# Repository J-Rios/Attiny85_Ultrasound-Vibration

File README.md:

# Attiny85_Ultrasound-Vibration
Attiny85 based system that read an ultrasound sensor and determines the distance by turning on a mini dc motor vibrator.
[See image.](Image.png)

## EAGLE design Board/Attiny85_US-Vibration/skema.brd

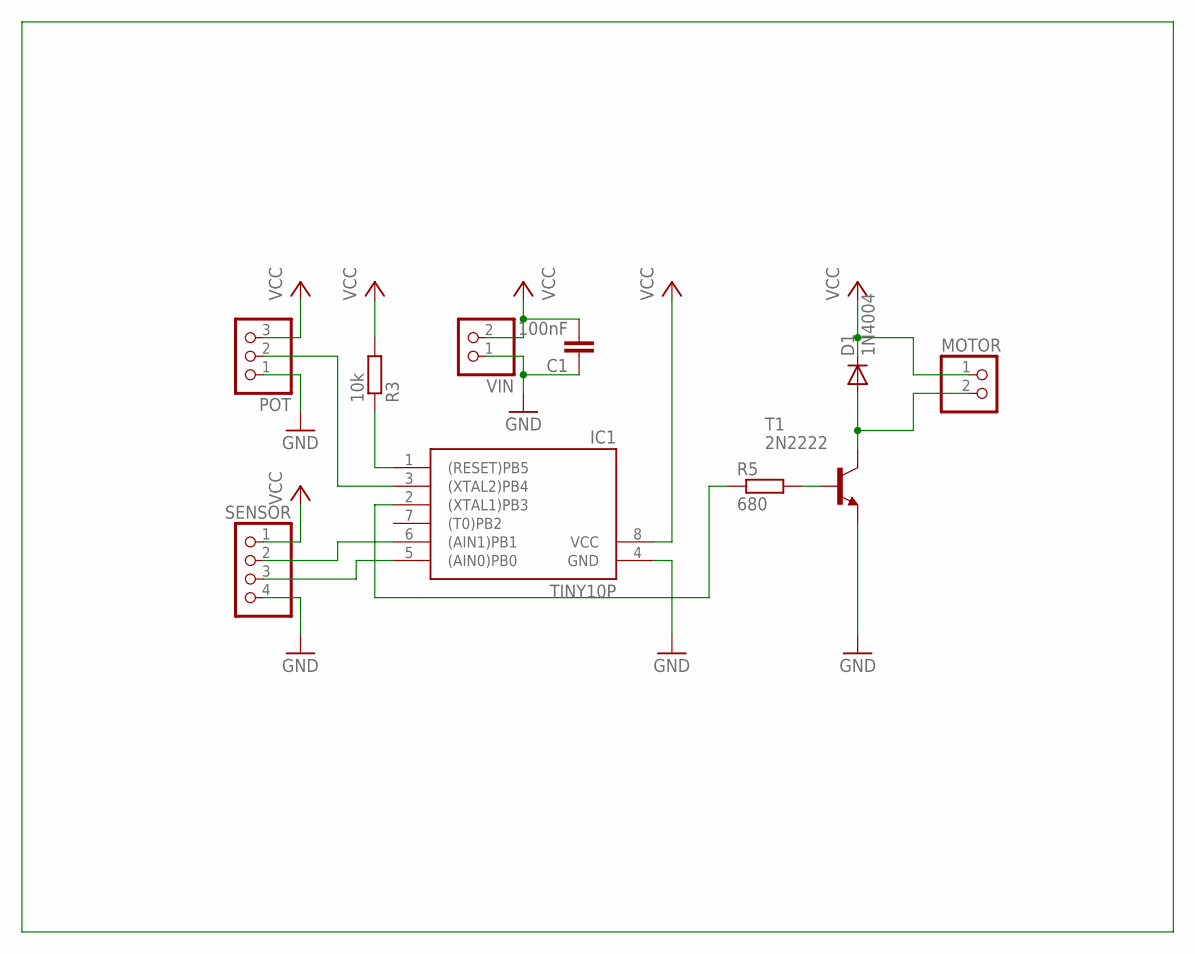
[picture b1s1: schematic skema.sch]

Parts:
C1: 100nF; C050-025X075
D1: 1N4004; DO41-10
IC1: TINY10P; DIL08
MOTOR: PINHD-1X2; 1X02
POT: PINHD-1X3; 1X03
R3: 10k; 0207/10
R5: 680; 0207/10
SENSOR: PINHD-1X4; 1X04
T1: 2N2222; TO18
VIN: PINHD-1X2; 1X02

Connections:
GND: C1.1, IC1.4 (GND), POT.1, SENSOR.4, T1.1 (E), VIN.1
unnamed: IC1.3 ((XTAL2)PB4), POT.2
unnamed: IC1.6 ((AIN1)PB1), SENSOR.2
unnamed: IC1.5 ((AIN0)PB0), SENSOR.3
unnamed: R5.2, T1.2 (B)
unnamed: IC1.1 ((RESET)PB5), R3.1
unnamed: D1.A, MOTOR.2, T1.3 (C)
unnamed: IC1.2 ((XTAL1)PB3), R5.1
VCC: C1.2, D1.C, IC1.8 (VCC), MOTOR.1, POT.3, R3.2, SENSOR.1, VIN.2

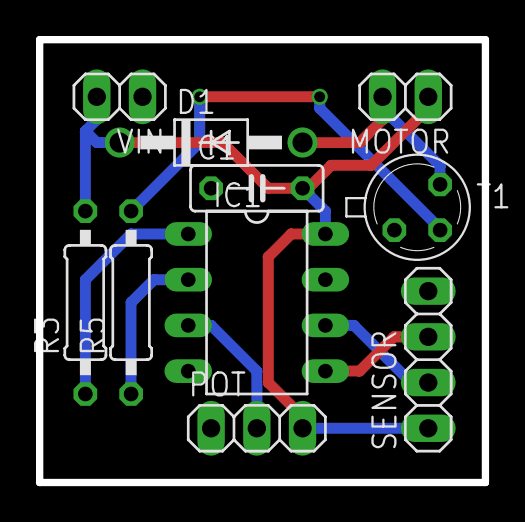
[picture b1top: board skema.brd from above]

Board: 2 copper layers, 24.8 x 24.6 mm, 10 parts (0 on the bottom side), 9 nets.

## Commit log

2015-04-27 Code
    Arduino code
2015-04-27 Board
    Eagle board
2015-05-10 Image
    Image added
2021-05-26 Spaces to Tabs
2021-05-26 Tab ident size of 4
